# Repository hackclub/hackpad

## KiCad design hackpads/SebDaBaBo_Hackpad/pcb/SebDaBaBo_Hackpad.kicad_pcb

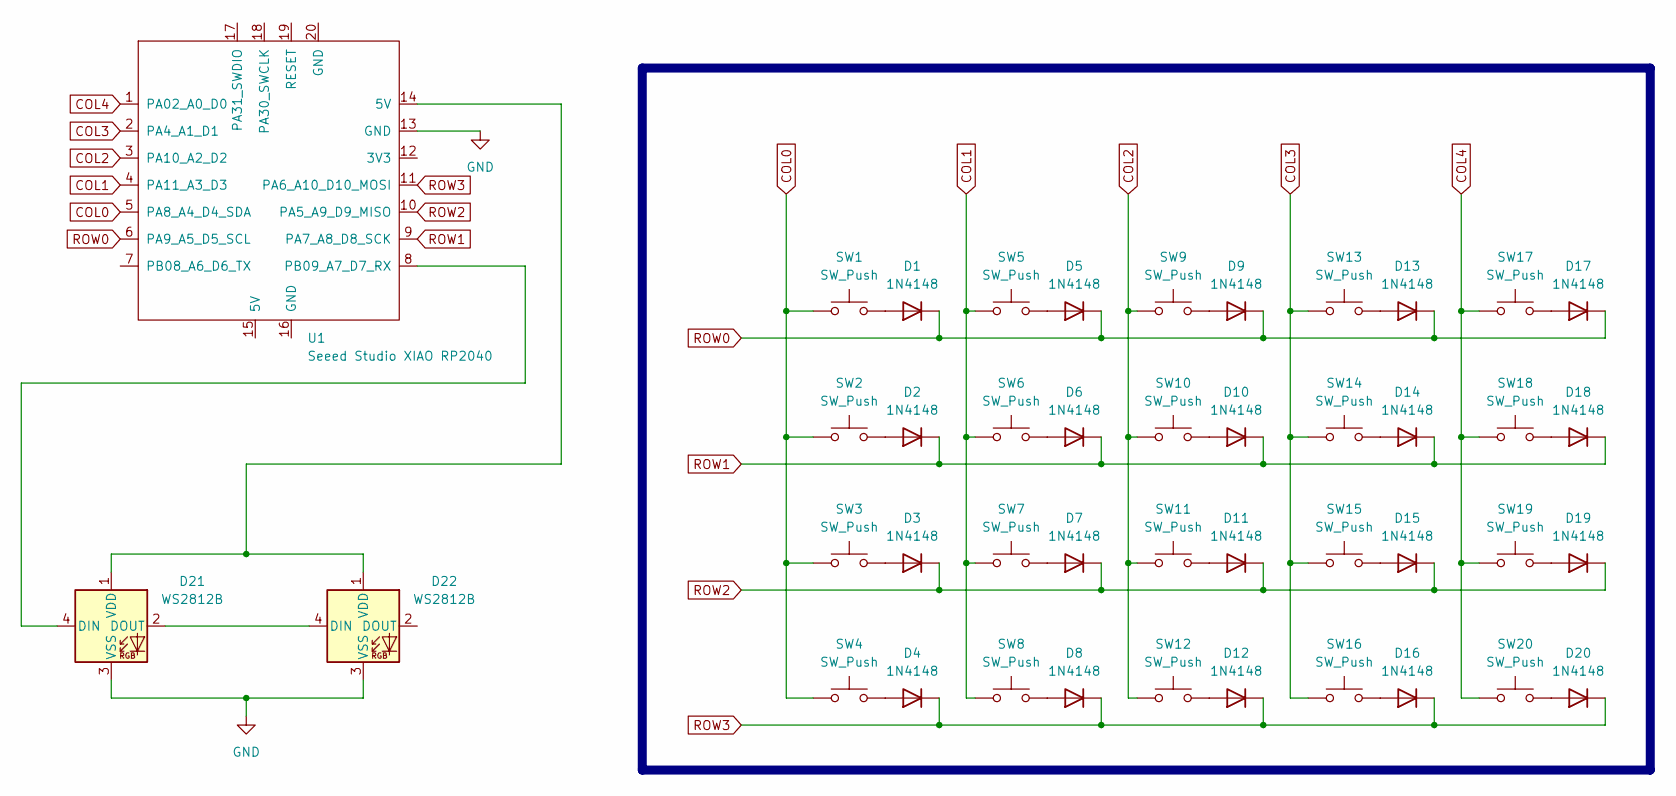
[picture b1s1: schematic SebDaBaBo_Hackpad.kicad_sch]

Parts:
D1, D2, D3, D4, D5, D6, D7, D8, D9, D10, D11, D12, D13, D14, D15, D16, D17, D18, D19, D20: 1N4148; D_DO-35_SOD27_P7.62mm_Horizontal
D21, D22: WS2812B; LED_WS2812B_PLCC4_5.0x5.0mm_P3.2mm
SW1, SW2, SW3, SW4, SW5, SW6, SW7, SW8, SW9, SW10, SW11, SW12, SW13, SW14, SW15, SW16, SW17, SW18, SW19, SW20: SW_Push; SW_Cherry_MX_1.00u_PCB
U1: Seeed Studio XIAO RP2040; XIAO-RP2040-DIP

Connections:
COL0: SW1.1, SW2.1, SW3.1, SW4.1, U1.5 (PA8_A4_D4_SDA)
COL1: SW5.1, SW6.1, SW7.1, SW8.1, U1.4 (PA11_A3_D3)
COL2: SW9.1, SW10.1, SW11.1, SW12.1, U1.3 (PA10_A2_D2)
COL3: SW13.1, SW14.1, SW15.1, SW16.1, U1.2 (PA4_A1_D1)
COL4: SW17.1, SW18.1, SW19.1, SW20.1, U1.1 (PA02_A0_D0)
GND: D21.3 (VSS), D22.3 (VSS), U1.13 (GND)
unnamed: D1.2 (A), SW1.2
unnamed: D2.2 (A), SW2.2
unnamed: D3.2 (A), SW3.2
unnamed: D4.2 (A), SW4.2
unnamed: D5.2 (A), SW5.2
unnamed: D6.2 (A), SW6.2
unnamed: D7.2 (A), SW7.2
unnamed: D8.2 (A), SW8.2
unnamed: D9.2 (A), SW9.2
unnamed: D10.2 (A), SW10.2
unnamed: D11.2 (A), SW11.2
unnamed: D12.2 (A), SW12.2
unnamed: D13.2 (A), SW13.2
unnamed: D14.2 (A), SW14.2
unnamed: D15.2 (A), SW15.2
unnamed: D16.2 (A), SW16.2
unnamed: D17.2 (A), SW17.2
unnamed: D18.2 (A), SW18.2
unnamed: D19.2 (A), SW19.2
unnamed: D20.2 (A), SW20.2
unnamed: D21.4 (DIN), U1.8 (PB09_A7_D7_RX)
unnamed: D21.2 (DOUT), D22.4 (DIN)
unnamed: D21.1 (VDD), D22.1 (VDD), U1.14 (5V)
ROW0: D1.1 (K), D5.1 (K), D9.1 (K), D13.1 (K), D17.1 (K), U1.6 (PA9_A5_D5_SCL)
ROW1: D2.1 (K), D6.1 (K), D10.1 (K), D14.1 (K), D18.1 (K), U1.9 (PA7_A8_D8_SCK)
ROW2: D3.1 (K), D7.1 (K), D11.1 (K), D15.1 (K), D19.1 (K), U1.10 (PA5_A9_D9_MISO)
ROW3: D4.1 (K), D8.1 (K), D12.1 (K), D16.1 (K), D20.1 (K), U1.11 (PA6_A10_D10_MOSI)

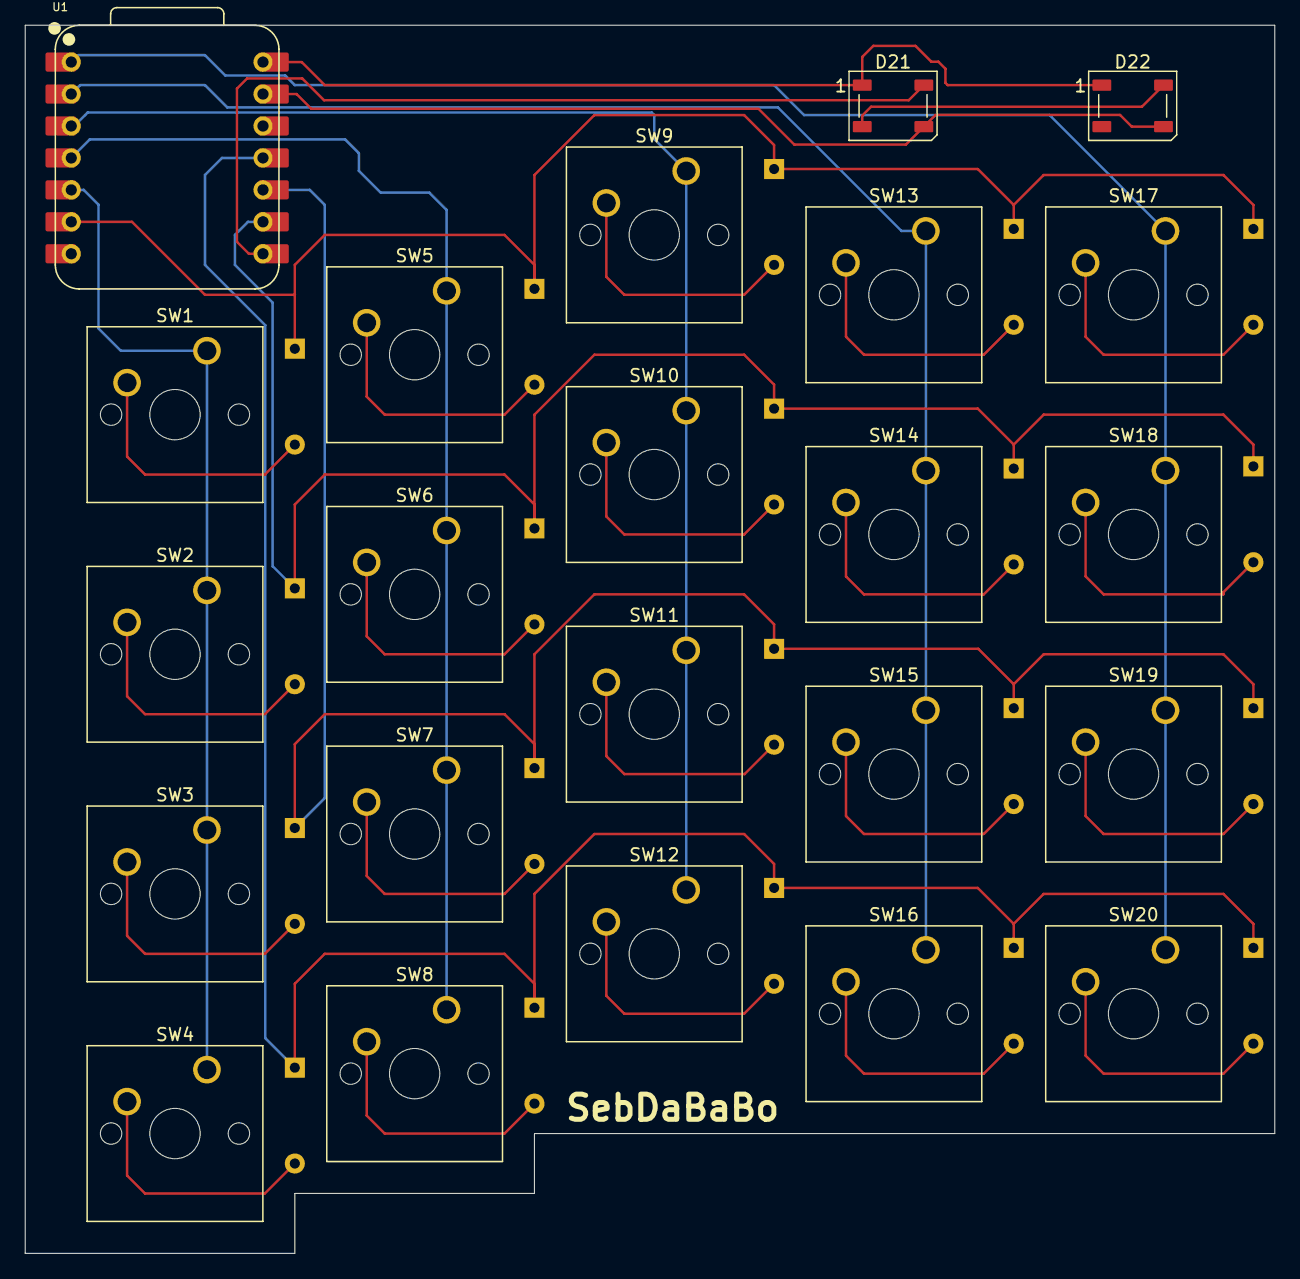
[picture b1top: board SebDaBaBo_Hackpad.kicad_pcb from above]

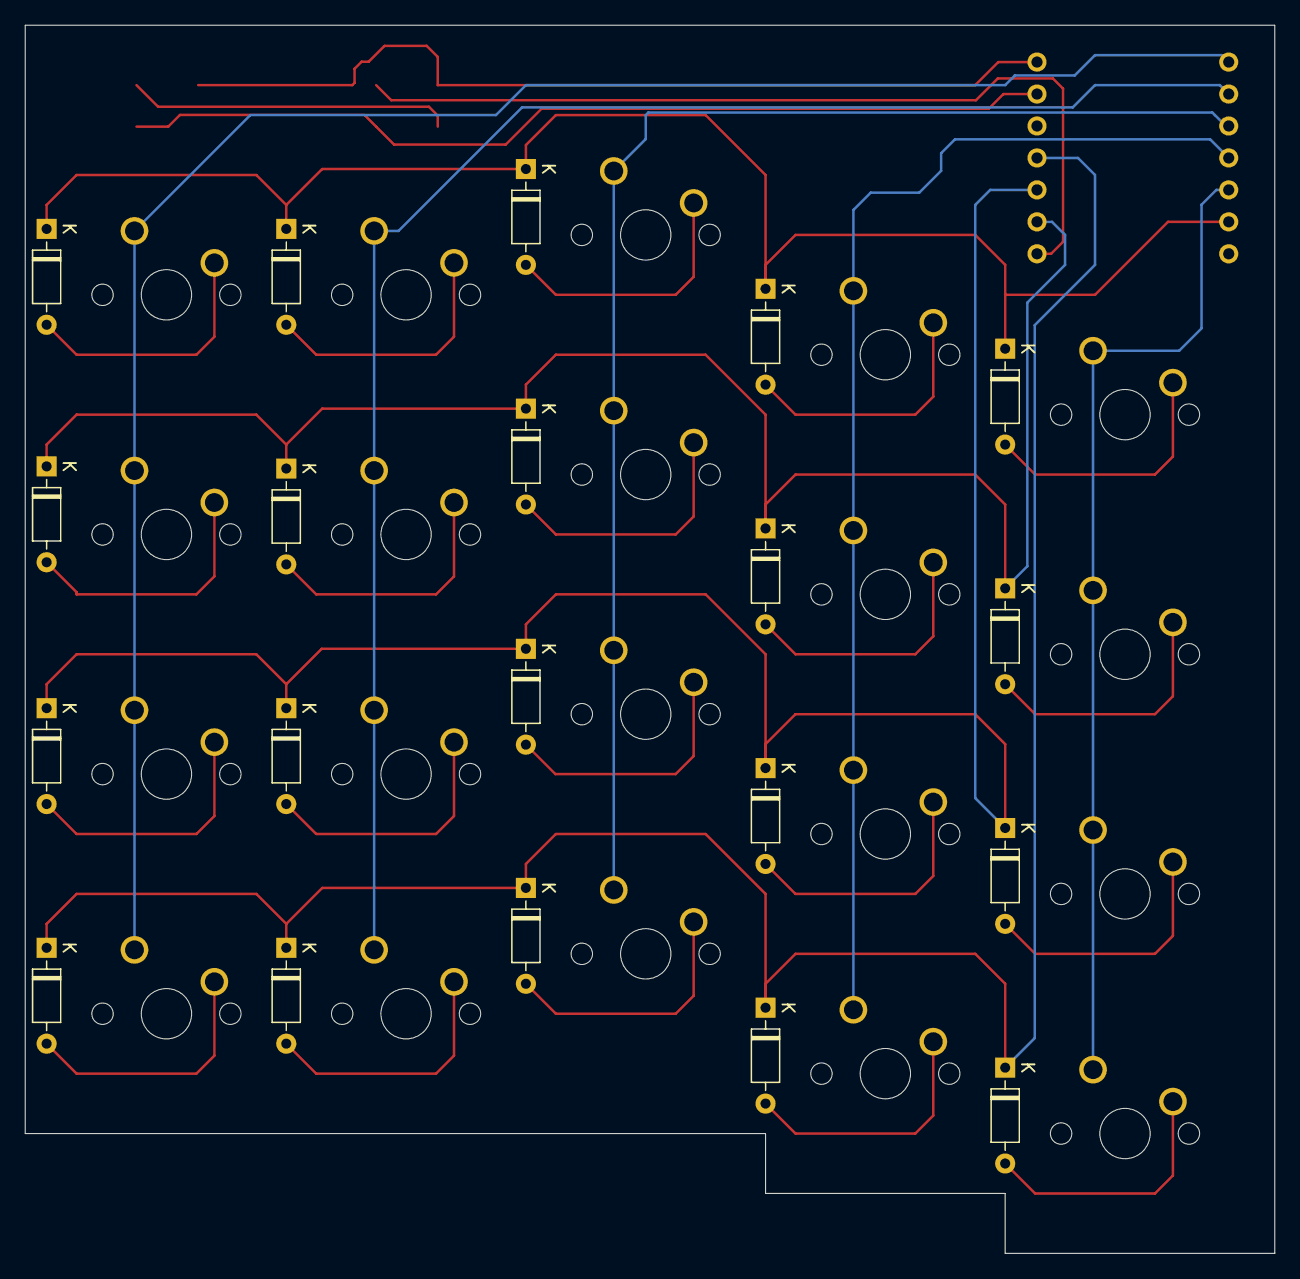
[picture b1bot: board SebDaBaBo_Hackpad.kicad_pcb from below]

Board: 2 copper layers, 99.3 x 97.6 mm, 43 parts (20 on the bottom side), 33 nets.

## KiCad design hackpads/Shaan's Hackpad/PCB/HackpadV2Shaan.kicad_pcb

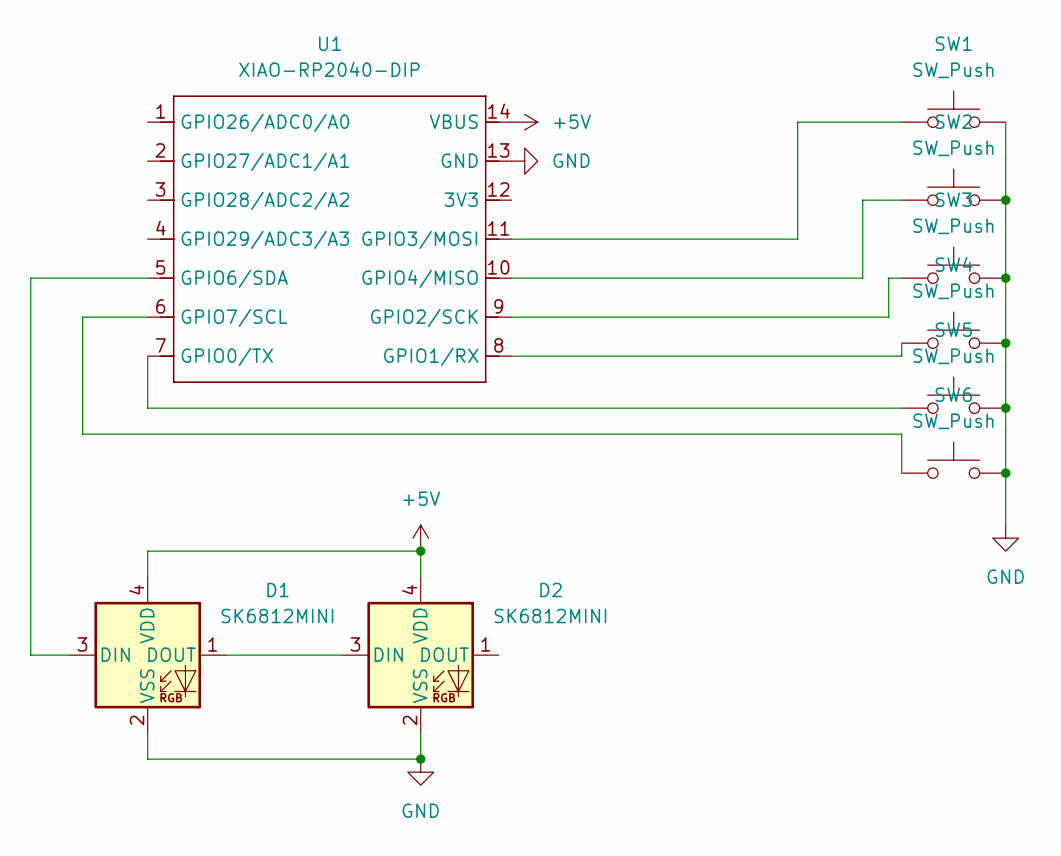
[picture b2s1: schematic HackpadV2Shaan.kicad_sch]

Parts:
D1, D2: SK6812MINI; LED_SK6812MINI_PLCC4_3.5x3.5mm_P1.75mm
SW1, SW2, SW3, SW4, SW5, SW6: SW_Push; SW_Cherry_MX_1.00u_PCB
U1: XIAO-RP2040-DIP

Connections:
+5V: D1.4 (VDD), D2.4 (VDD), U1.14 (VBUS)
GND: D1.2 (VSS), D2.2 (VSS), SW1.2, SW2.2, SW3.2, SW4.2, SW5.2, SW6.2, U1.13 (GND)
unnamed: D1.3 (DIN), U1.5 (GPIO6/SDA)
unnamed: D1.1 (DOUT), D2.3 (DIN)
unnamed: SW5.1, U1.7 (GPIO0/TX)
unnamed: SW4.1, U1.8 (GPIO1/RX)
unnamed: SW3.1, U1.9 (GPIO2/SCK)
unnamed: SW1.1, U1.11 (GPIO3/MOSI)
unnamed: SW2.1, U1.10 (GPIO4/MISO)
unnamed: SW6.1, U1.6 (GPIO7/SCL)

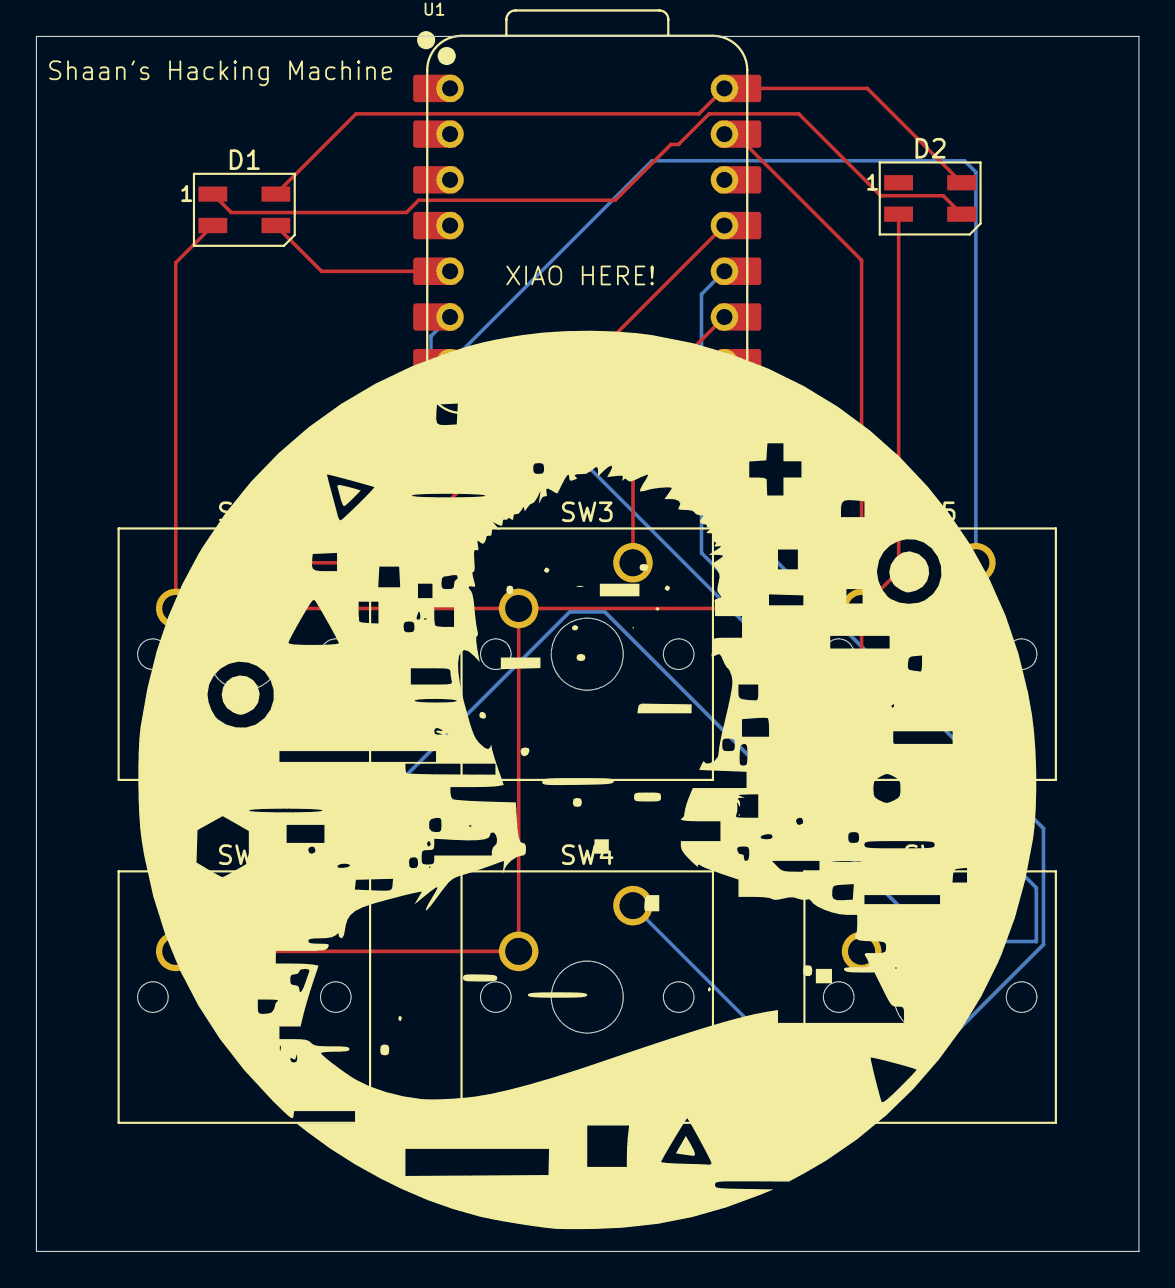
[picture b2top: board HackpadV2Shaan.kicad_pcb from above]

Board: 2 copper layers, 61.2 x 67.5 mm, 9 parts (0 on the bottom side), 10 nets.

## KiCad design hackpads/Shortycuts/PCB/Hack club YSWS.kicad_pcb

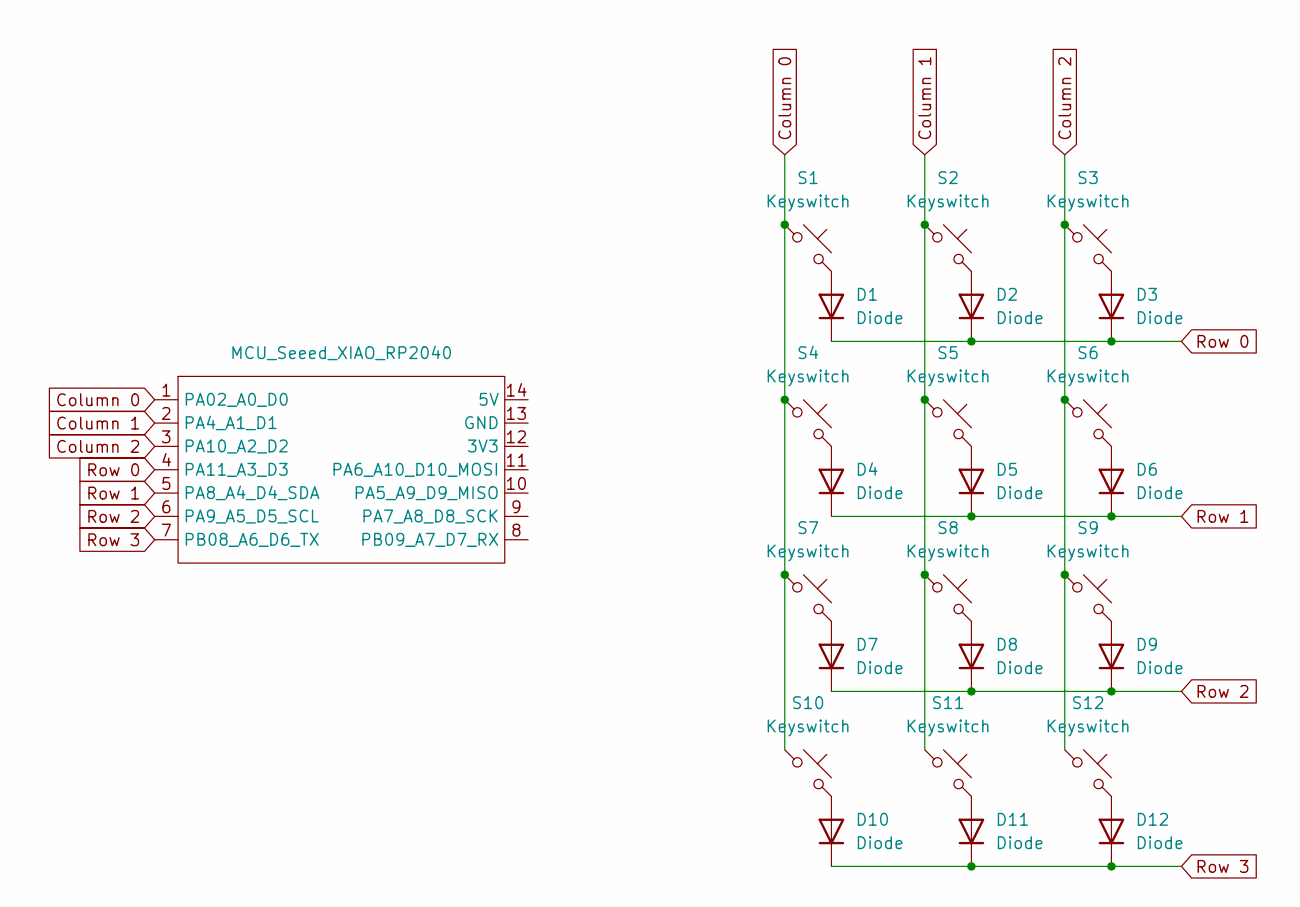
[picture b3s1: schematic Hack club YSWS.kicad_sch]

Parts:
D1, D2, D3, D4, D5, D6, D7, D8, D9, D10, D11, D12: Diode; Diode_DO-35
S1, S2, S3, S4, S5, S6, S7, S8, S9, S10, S11, S12: Keyswitch; MX_PCB_1.00u
U1: MCU_Seeed_XIAO_RP2040; Seeed_XIAO_RP2040

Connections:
Column 0: S1.1, S4.1, S7.1, S10.1, U1.1 (PA02_A0_D0)
Column 1: S2.1, S5.1, S8.1, S11.1, U1.2 (PA4_A1_D1)
Column 2: S3.1, S6.1, S9.1, S12.1, U1.3 (PA10_A2_D2)
unnamed: D1.2 (A), S1.2
unnamed: D2.2 (A), S2.2
unnamed: D3.2 (A), S3.2
unnamed: D4.2 (A), S4.2
unnamed: D5.2 (A), S5.2
unnamed: D6.2 (A), S6.2
unnamed: D7.2 (A), S7.2
unnamed: D8.2 (A), S8.2
unnamed: D9.2 (A), S9.2
unnamed: D10.2 (A), S10.2
unnamed: D11.2 (A), S11.2
unnamed: D12.2 (A), S12.2
Row 0: D1.1 (K), D2.1 (K), D3.1 (K), U1.4 (PA11_A3_D3)
Row 1: D4.1 (K), D5.1 (K), D6.1 (K), U1.5 (PA8_A4_D4_SDA)
Row 2: D7.1 (K), D8.1 (K), D9.1 (K), U1.6 (PA9_A5_D5_SCL)
Row 3: D10.1 (K), D11.1 (K), D12.1 (K), U1.7 (PB08_A6_D6_TX)

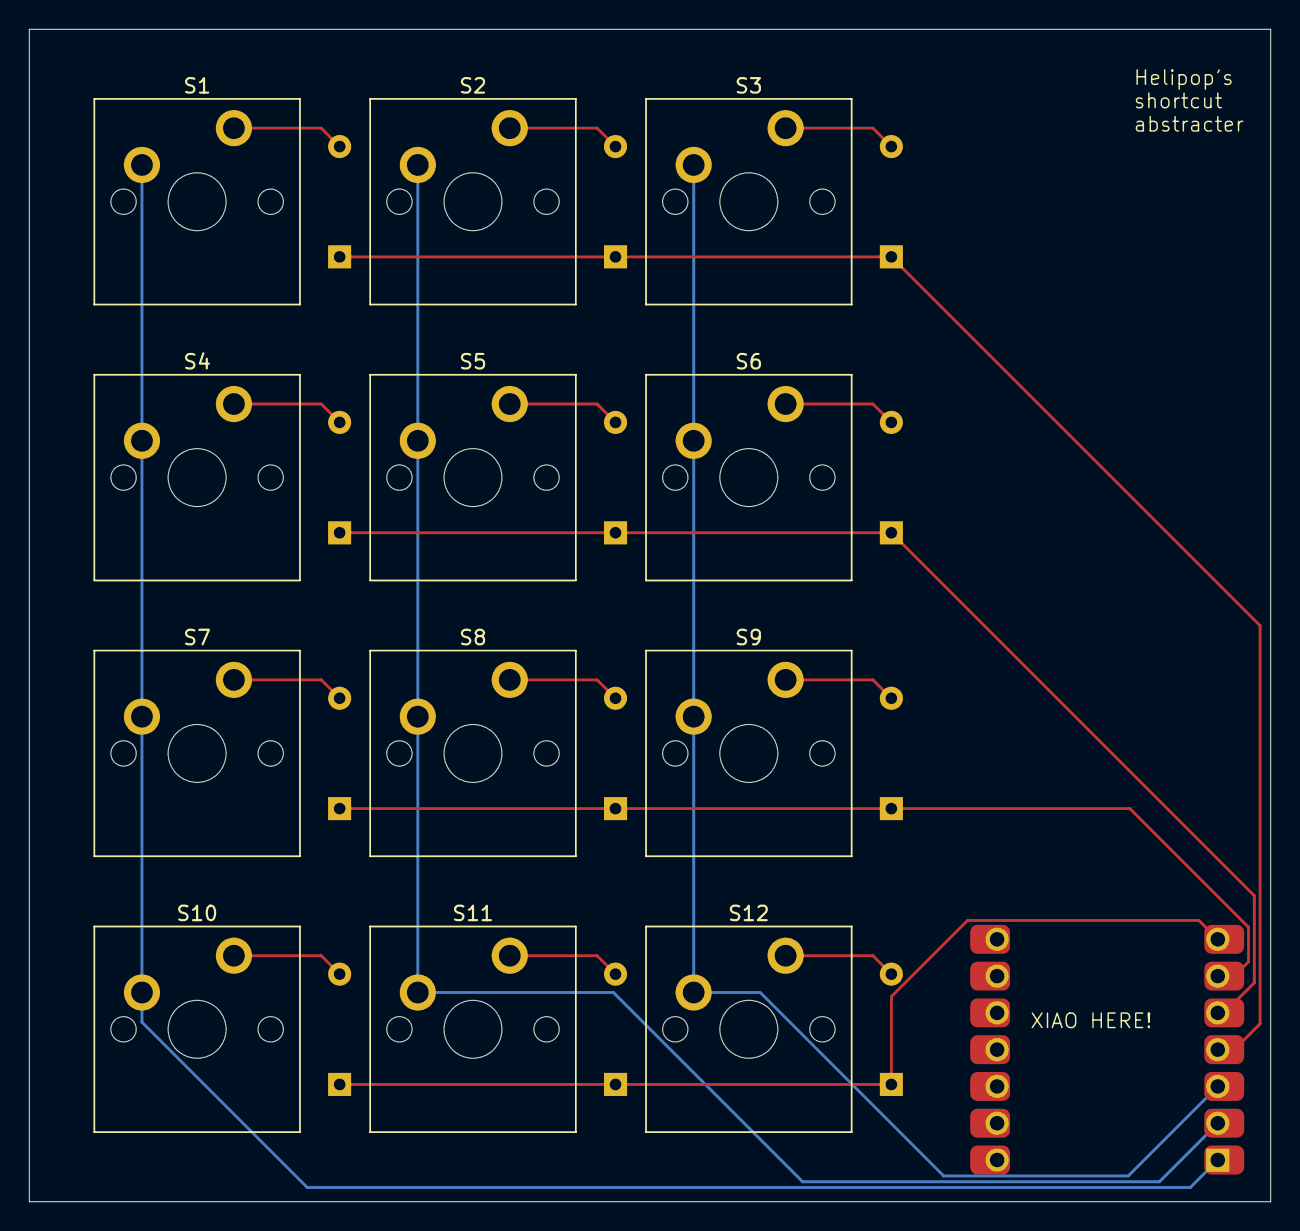
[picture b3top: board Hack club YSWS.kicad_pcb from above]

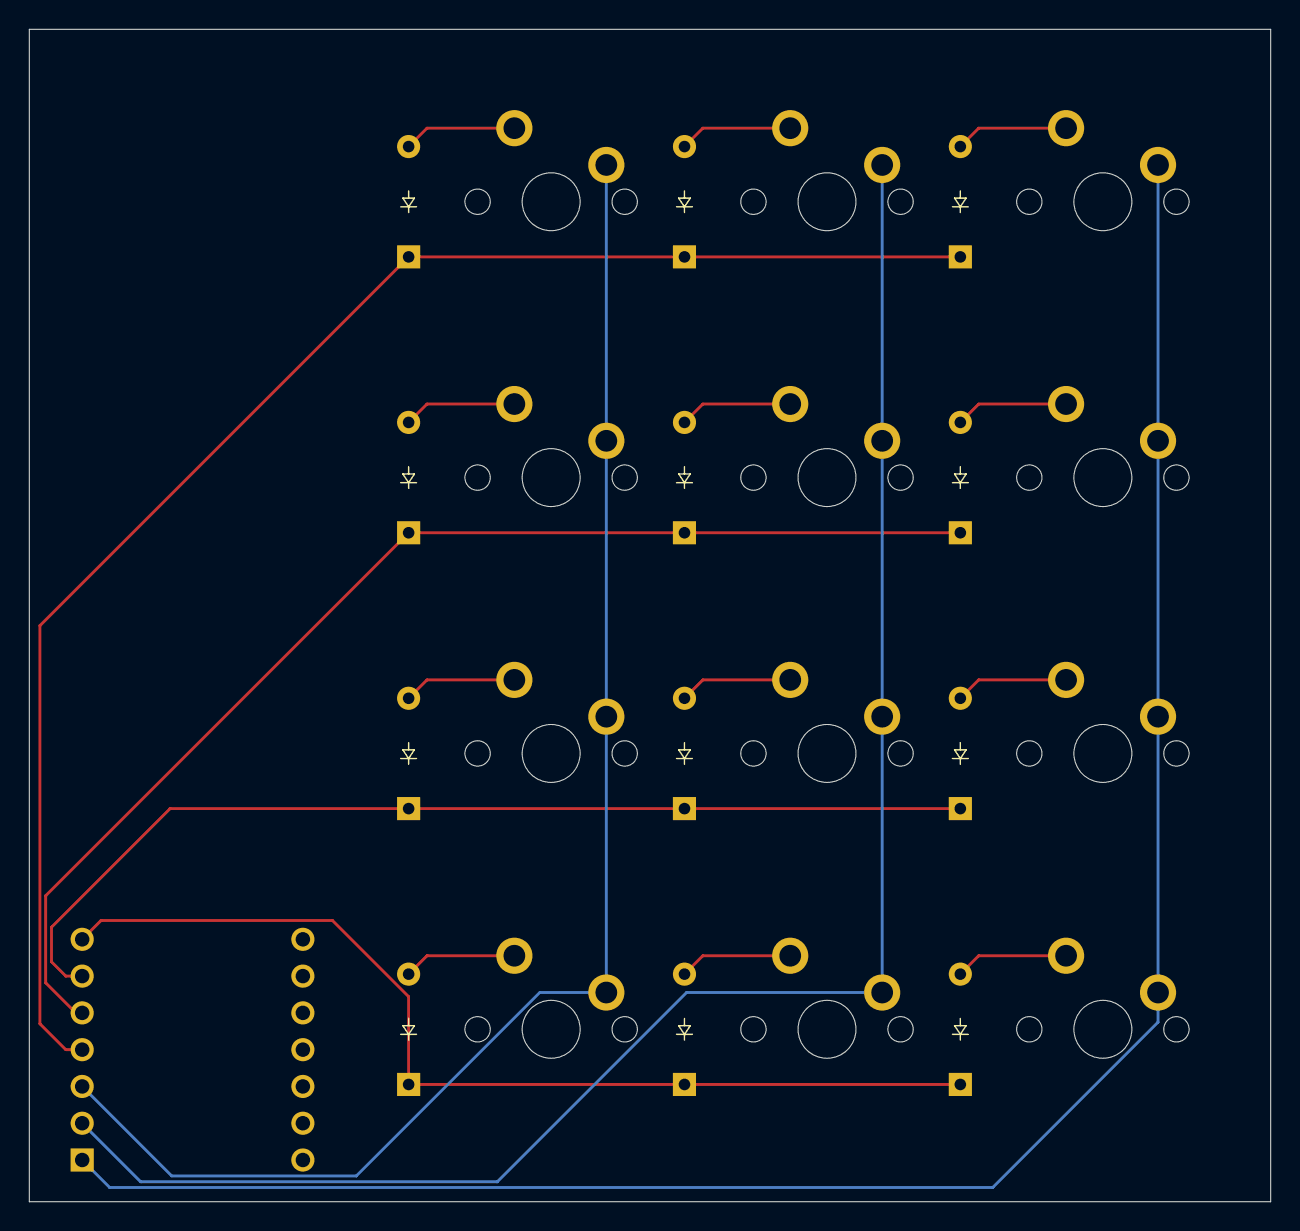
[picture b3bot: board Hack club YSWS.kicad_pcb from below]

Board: 2 copper layers, 85.7 x 81.0 mm, 25 parts (12 on the bottom side), 19 nets.

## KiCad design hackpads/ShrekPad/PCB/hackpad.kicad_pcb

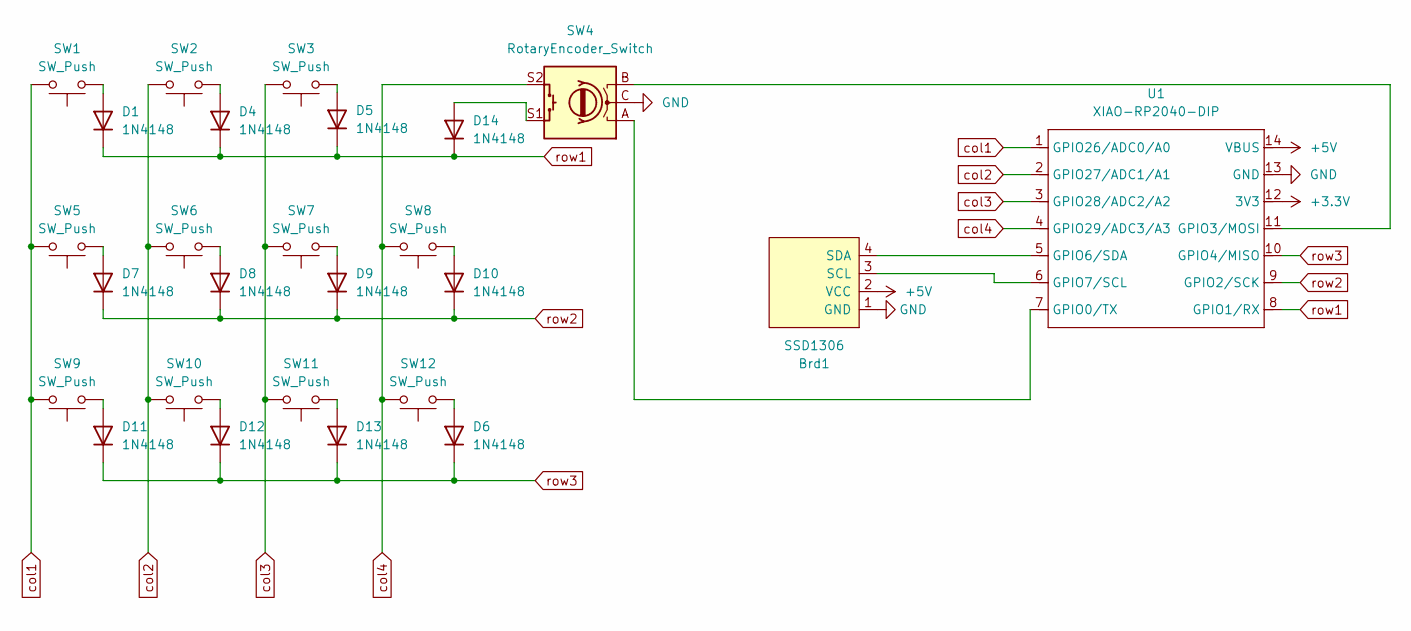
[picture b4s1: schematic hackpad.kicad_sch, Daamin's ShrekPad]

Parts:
Brd1: SSD1306; 128x64OLED
D1, D4, D5, D6, D7, D8, D9, D10, D11, D12, D13, D14: 1N4148; D_DO-35_SOD27_P7.62mm_Horizontal
SW1, SW2, SW3, SW5, SW6, SW7, SW8, SW9, SW10, SW11, SW12: SW_Push; SW_Cherry_MX_1.00u_PCB
SW4: RotaryEncoder_Switch; RotaryEncoder_Alps_EC11E-Switch_Vertical_H20mm_CircularMoun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
U1: XIAO-RP2040-DIP

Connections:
+3.3V: U1.12 (3V3)
+5V: Brd1.2 (VCC), U1.14 (VBUS)
GND: Brd1.1 (GND), SW4.C, U1.13 (GND)
unnamed: Brd1.3 (SCL), U1.6 (GPIO7/SCL)
unnamed: Brd1.4 (SDA), U1.5 (GPIO6/SDA)
unnamed: D1.2 (A), SW1.2
unnamed: D4.2 (A), SW2.2
unnamed: D5.2 (A), SW3.2
unnamed: D6.2 (A), SW12.2
unnamed: D7.2 (A), SW5.2
unnamed: D8.2 (A), SW6.2
unnamed: D9.2 (A), SW7.2
unnamed: D10.2 (A), SW8.2
unnamed: D11.2 (A), SW9.2
unnamed: D12.2 (A), SW10.2
unnamed: D13.2 (A), SW11.2
unnamed: D14.2 (A), SW4.S1
unnamed: SW4.A, U1.7 (GPIO0/TX)
unnamed: SW4.B, U1.11 (GPIO3/MOSI)
col1: SW1.1, SW5.1, SW9.1, U1.1 (GPIO26/ADC0/A0)
col2: SW2.1, SW6.1, SW10.1, U1.2 (GPIO27/ADC1/A1)
col3: SW3.1, SW7.1, SW11.1, U1.3 (GPIO28/ADC2/A2)
col4: SW4.S2, SW8.1, SW12.1, U1.4 (GPIO29/ADC3/A3)
row1: D1.1 (K), D4.1 (K), D5.1 (K), D14.1 (K), U1.8 (GPIO1/RX)
row2: D7.1 (K), D8.1 (K), D9.1 (K), D10.1 (K), U1.9 (GPIO2/SCK)
row3: D6.1 (K), D11.1 (K), D12.1 (K), D13.1 (K), U1.10 (GPIO4/MISO)

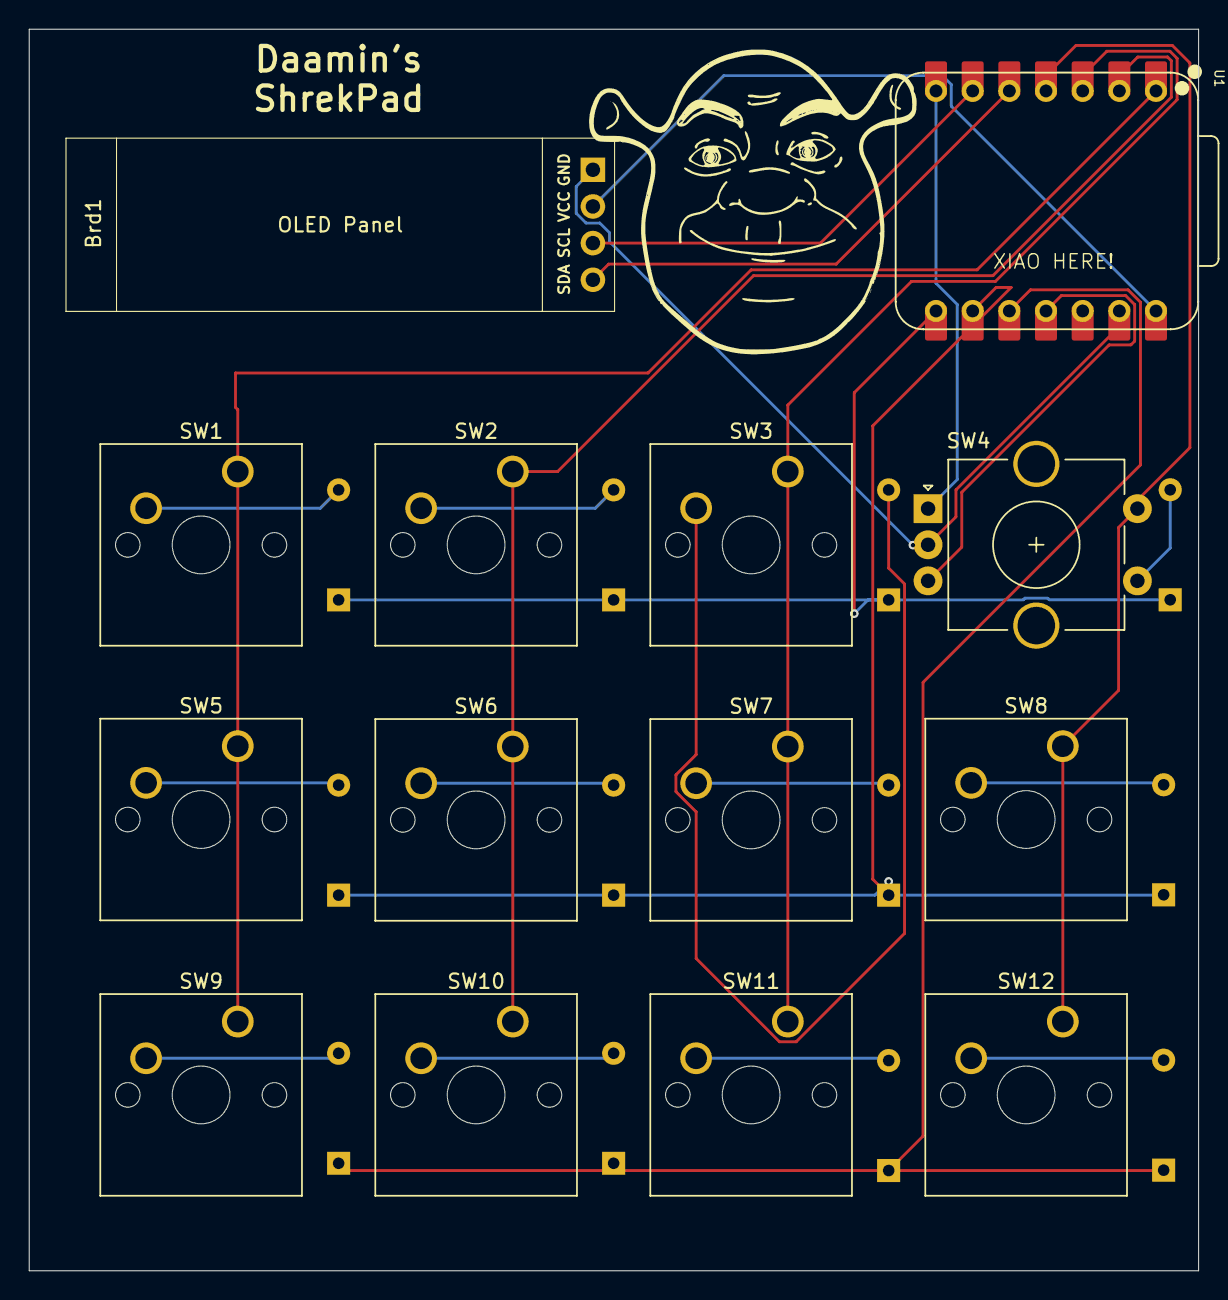
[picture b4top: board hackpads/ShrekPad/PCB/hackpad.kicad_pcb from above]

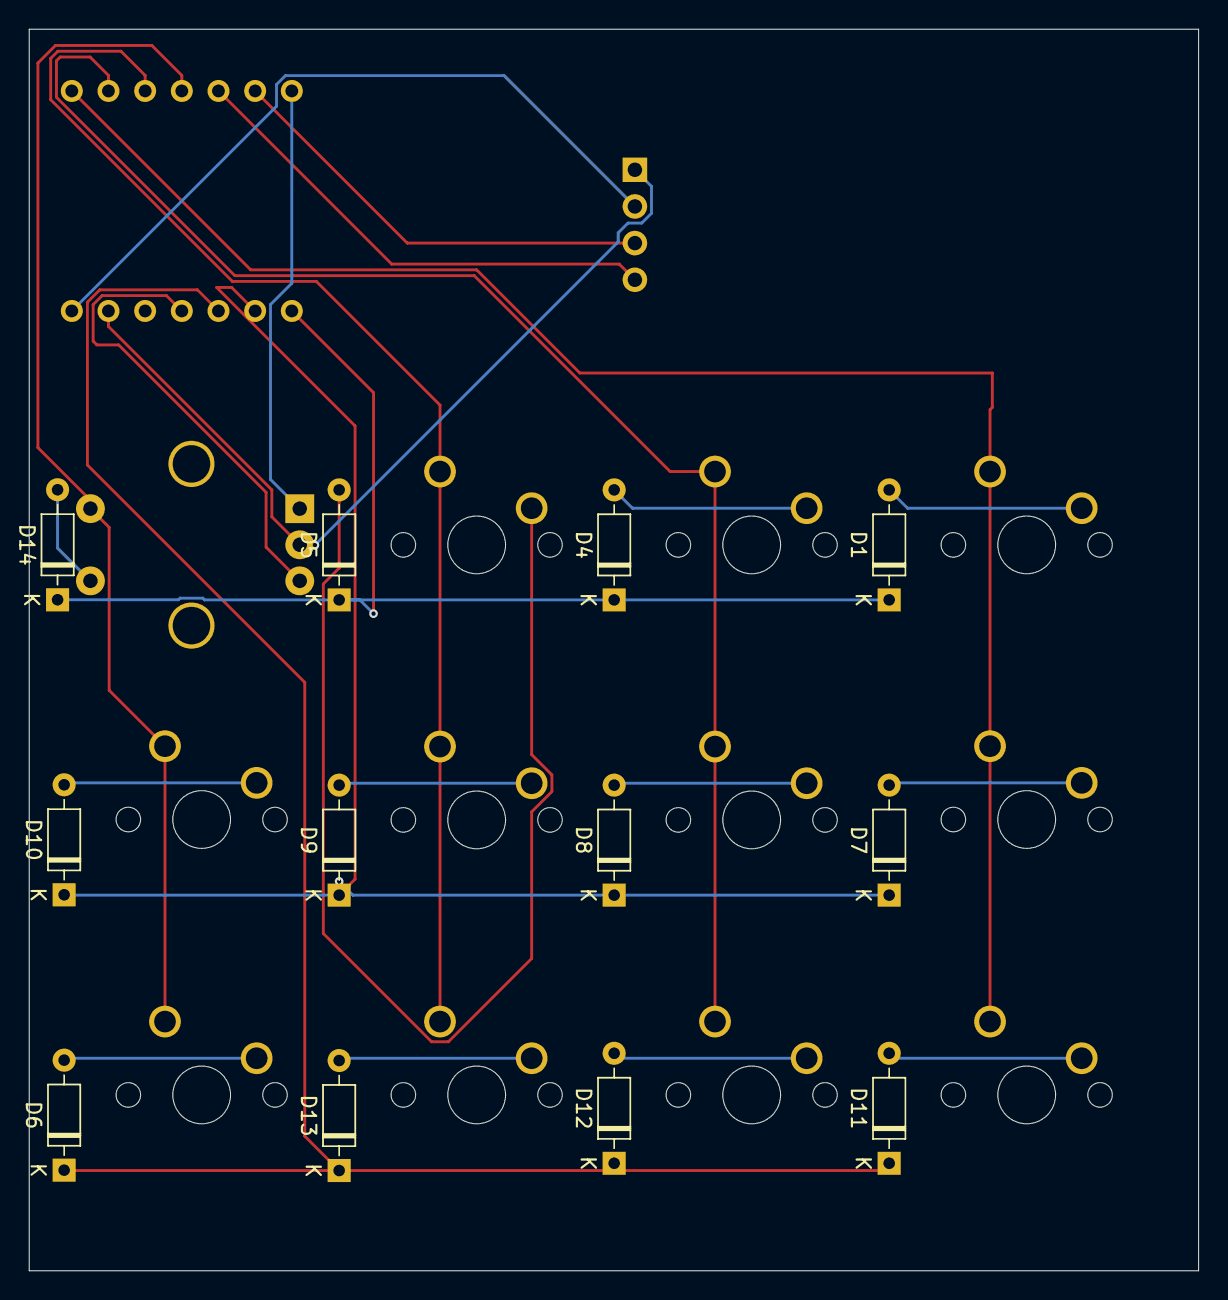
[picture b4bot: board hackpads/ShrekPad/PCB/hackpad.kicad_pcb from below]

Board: 2 copper layers, 81.0 x 86.0 mm, 26 parts (12 on the bottom side), 25 nets.

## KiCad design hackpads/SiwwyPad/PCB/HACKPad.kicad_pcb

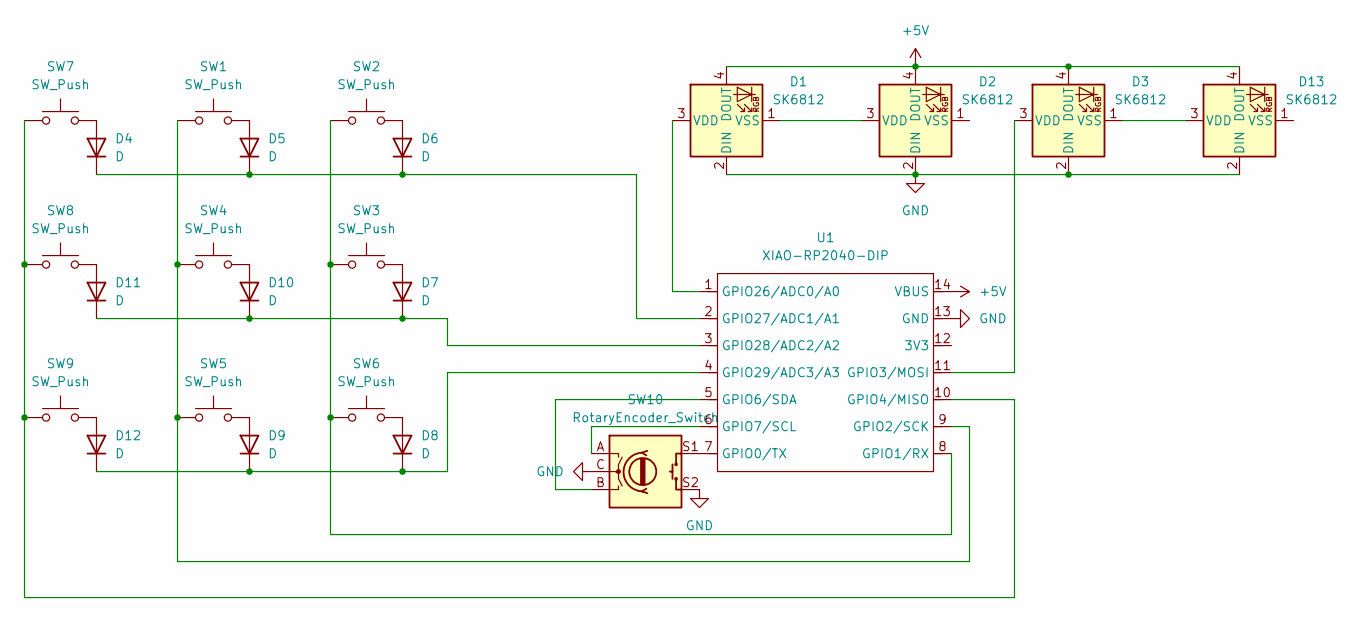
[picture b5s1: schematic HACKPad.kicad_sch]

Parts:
D1, D2, D3, D13: SK6812; LED_SK6812_PLCC4_5.0x5.0mm_P3.2mm
D4, D5, D6, D7, D8, D9, D10, D11, D12: D; D_DO-35_SOD27_P7.62mm_Horizontal
SW1, SW2, SW3, SW4, SW5, SW6, SW7, SW8, SW9: SW_Push; SW_Cherry_MX_1.00u_PCB
SW10: RotaryEncoder_Switch; RotaryEncoder_Alps_EC11E-Switch_Vertical_H20mm_CircularMoun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
U1: XIAO-RP2040-DIP

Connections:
+5V: D1.4 (DOUT), D2.4 (DOUT), D3.4 (DOUT), D13.4 (DOUT), U1.14 (VBUS)
GND: D1.2 (DIN), D2.2 (DIN), D3.2 (DIN), D13.2 (DIN), SW10.C, SW10.S2, U1.13 (GND)
unnamed: D1.3 (VDD), U1.1 (GPIO26/ADC0/A0)
unnamed: D1.1 (VSS), D2.3 (VDD)
unnamed: D3.3 (VDD), U1.11 (GPIO3/MOSI)
unnamed: D4.2 (A), SW7.2
unnamed: D4.1 (K), D5.1 (K), D6.1 (K), U1.2 (GPIO27/ADC1/A1)
unnamed: D5.2 (A), SW1.2
unnamed: D6.2 (A), SW2.2
unnamed: D7.2 (A), SW3.2
unnamed: D8.2 (A), SW6.2
unnamed: D9.2 (A), SW5.2
unnamed: D10.2 (A), SW4.2
unnamed: D7.1 (K), D10.1 (K), D11.1 (K), U1.3 (GPIO28/ADC2/A2)
unnamed: D11.2 (A), SW8.2
unnamed: D12.2 (A), SW9.2
unnamed: D8.1 (K), D9.1 (K), D12.1 (K), U1.4 (GPIO29/ADC3/A3)
unnamed: D3.1 (VSS), D13.3 (VDD)
unnamed: SW10.S1, U1.7 (GPIO0/TX)
unnamed: SW2.1, SW3.1, SW6.1, U1.8 (GPIO1/RX)
unnamed: SW1.1, SW4.1, SW5.1, U1.9 (GPIO2/SCK)
unnamed: SW7.1, SW8.1, SW9.1, U1.10 (GPIO4/MISO)
unnamed: SW10.B, U1.5 (GPIO6/SDA)
unnamed: SW10.A, U1.6 (GPIO7/SCL)
